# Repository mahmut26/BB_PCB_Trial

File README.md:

This was my PSU design...

The .zip contains more of it with current control etc.

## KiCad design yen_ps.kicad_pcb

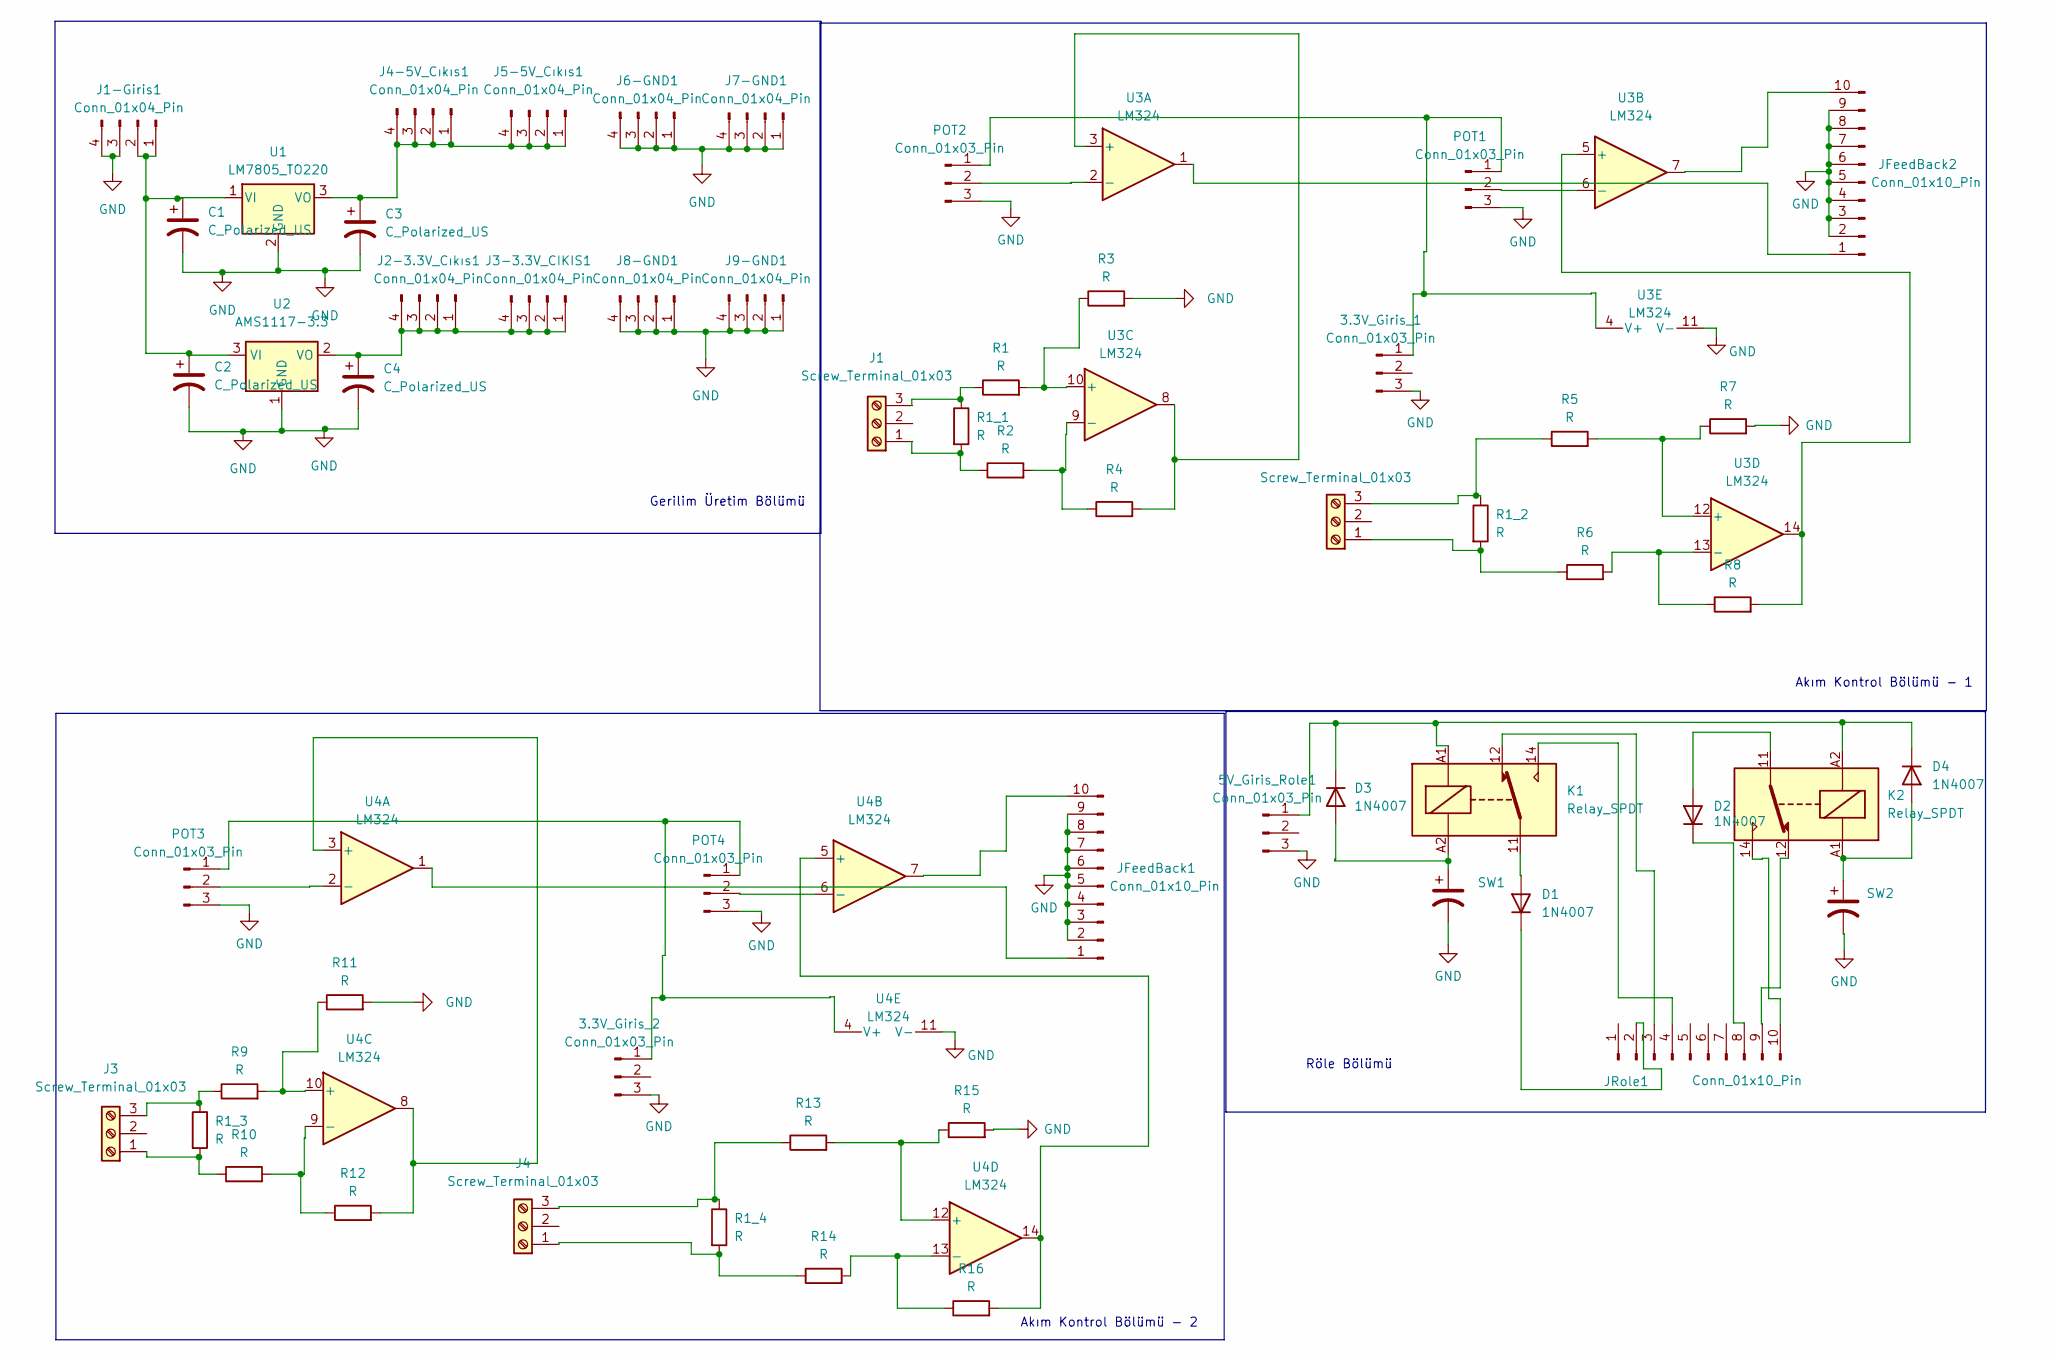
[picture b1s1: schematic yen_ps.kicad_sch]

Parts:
3.3V_Giris_1, 3.3V_Giris_2, 5V_Giris_Role1: Conn_01x03_Pin; FanPinHeader_1x03_P2.54mm_Vertical
C1, C2, C3, C4: C_Polarized_US; CP_Radial_D10.0mm_P5.00mm
D1, D2, D3, D4: 1N4007; D_DO-41_SOD81_P10.16mm_Horizontal
J1, J2, J3, J4: Screw_Terminal_01x03; TerminalBlock_MetzConnect_Type011_RT05503HBWC_1x03_P5.00mm_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
J1-Giris1, J2-3.3V_Cıkıs1, J3-3.3V_CIKIS1, J4-5V_Cıkıs1, J5-5V_Cıkıs1, J6-GND1, J7-GND1, J8-GND1, J9-GND1: Conn_01x04_Pin; FanPinHeader_1x04_P2.54mm_Vertical
JFeedBack1, JFeedBack2: Conn_01x10_Pin; PinHeader_1x10_P2.54mm_Vertical
JRole1: Conn_01x10_Pin; PinHeader_1x10_P2.54mm_Vertical
K1, K2: Relay_SPDT; Relay_SPDT_Finder_36.11
POT1, POT2, POT3, POT4: Conn_01x03_Pin; FanPinHeader_1x03_P2.54mm_Vertical
R1, R2, R3, R4, R5, R6, R7, R8, R9, R10, R11, R12, R13, R14, R15, R16: R; R_Axial_DIN0207_L6.3mm_D2.5mm_P15.24mm_Horizontal
R1_1, R1_2, R1_3, R1_4: R; R_Axial_Power_L20.0mm_W6.4mm_P22.40mm
SW1, SW2: C_Polarized_US; CP_Axial_L10.0mm_D4.5mm_P15.00mm_Horizontal
U1: LM7805_TO220; TO-220-3_Vertical
U2: AMS1117-3.3; SOT-223-3_TabPin2
U3, U4: LM324; SOIC-14_3.9x8.7mm_P1.27mm

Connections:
GND: 3.3V_Giris_1.3, 3.3V_Giris_2.3, 5V_Giris_Role1.3, C1.2, C2.2, C3.2, C4.2, J1-Giris1.3, J1-Giris1.4, JFeedBack1.2, JFeedBack1.3, JFeedBack1.4, JFeedBack1.5, JFeedBack1.6, JFeedBack1.7, JFeedBack1.8, JFeedBack1.9, JFeedBack2.2, JFeedBack2.3, JFeedBack2.4, JFeedBack2.5, JFeedBack2.6, JFeedBack2.7, JFeedBack2.8, JFeedBack2.9, POT1.3, POT2.3, POT3.3, POT4.3, R3.2, R7.2, R11.2, R15.2, SW1.2, SW2.2, U1.2 (GND), U2.1 (GND), U3.11 (V-), U4.11 (V-)
unnamed: 3.3V_Giris_1.1, POT1.1, POT2.1, U3.4 (V+)
unnamed: 3.3V_Giris_2.1, POT3.1, POT4.1, U4.4 (V+)
unnamed: 5V_Giris_Role1.1, D3.1 (K), D4.1 (K), K1.A1, K2.A2
unnamed: D1.2 (A), K1.11
unnamed: D1.1 (K), JRole1.2
unnamed: D2.2 (A), K2.11
unnamed: D2.1 (K), JRole1.8
unnamed: D3.2 (A), K1.A2, SW1.1
unnamed: D4.2 (A), K2.A1, SW2.1
unnamed: C1.1, C2.1, J1-Giris1.1, J1-Giris1.2, U1.1 (VI), U2.3 (VI)
unnamed: J1.1, R1_1.2, R2.1
unnamed: J1.3, R1.1, R1_1.1
unnamed: C4.1, J2-3.3V_Cıkıs1.1, J2-3.3V_Cıkıs1.2, J2-3.3V_Cıkıs1.3, J2-3.3V_Cıkıs1.4, J3-3.3V_CIKIS1.1, J3-3.3V_CIKIS1.2, J3-3.3V_CIKIS1.3, J3-3.3V_CIKIS1.4, U2.2 (VO)
unnamed: J2.1, R1_2.2, R6.1
unnamed: J2.3, R1_2.1, R5.1
unnamed: J3.1, R1_3.2, R10.1
unnamed: J3.3, R1_3.1, R9.1
unnamed: C3.1, J4-5V_Cıkıs1.1, J4-5V_Cıkıs1.2, J4-5V_Cıkıs1.3, J4-5V_Cıkıs1.4, J5-5V_Cıkıs1.1, J5-5V_Cıkıs1.2, J5-5V_Cıkıs1.3, J5-5V_Cıkıs1.4, U1.3 (VO)
unnamed: J4.1, R1_4.2, R14.1
unnamed: J4.3, R1_4.1, R13.1
unnamed: JFeedBack1.1, U4.1
unnamed: JFeedBack1.10, U4.7
unnamed: JFeedBack2.1, U3.1
unnamed: JFeedBack2.10, U3.7
unnamed: JRole1.3, K1.12
unnamed: JRole1.4, K1.14
unnamed: JRole1.9, K2.12
unnamed: JRole1.10, K2.14
unnamed: POT1.2, U3.6 (-)
unnamed: POT2.2, U3.2 (-)
unnamed: POT3.2, U4.2 (-)
unnamed: POT4.2, U4.6 (-)
unnamed: R4.2, U3.3 (+), U3.8
unnamed: R8.2, U3.5 (+), U3.14
unnamed: R1.2, R3.1, U3.10 (+)
unnamed: R2.2, R4.1, U3.9 (-)
unnamed: R5.2, R7.1, U3.12 (+)
unnamed: R6.2, R8.1, U3.13 (-)
unnamed: R12.2, U4.3 (+), U4.8
unnamed: R16.2, U4.5 (+), U4.14
unnamed: R9.2, R11.1, U4.10 (+)
unnamed: R10.2, R12.1, U4.9 (-)
unnamed: R13.2, R15.1, U4.12 (+)
unnamed: R14.2, R16.1, U4.13 (-)

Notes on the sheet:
Akım Kontrol Bölümü - 1
Gerilim Üretim Bölümü
Akım Kontrol Bölümü - 2
Röle Bölümü

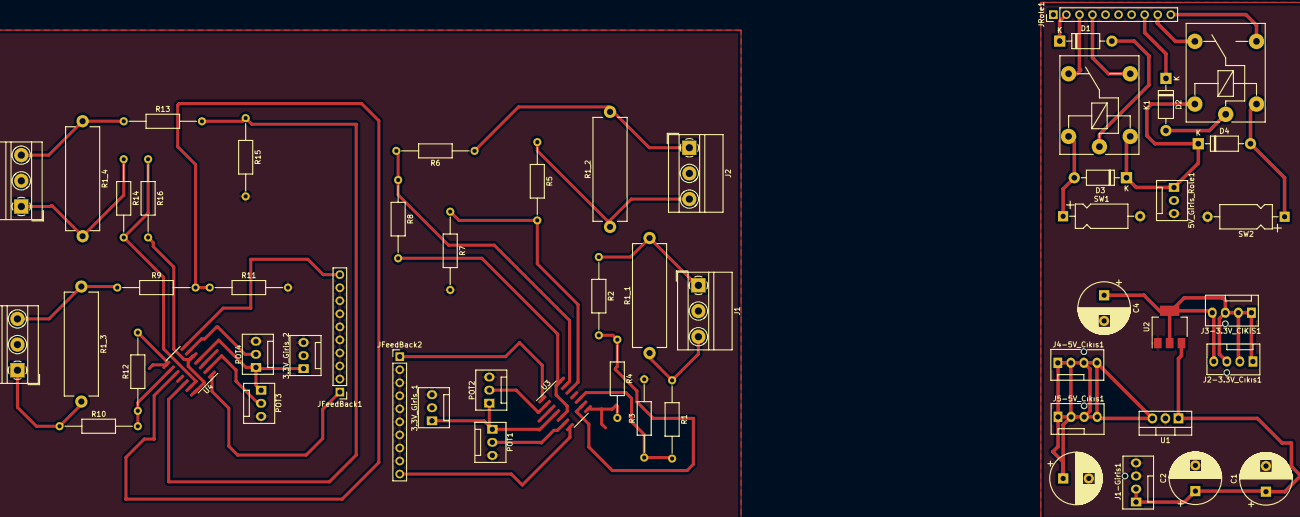
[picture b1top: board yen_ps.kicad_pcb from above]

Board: 2 copper layers, 55 parts (0 on the bottom side), 45 nets.

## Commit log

2024-11-30 Add files via upload
    KiCad Files Added
2024-11-30 Create yen_ps-backups
